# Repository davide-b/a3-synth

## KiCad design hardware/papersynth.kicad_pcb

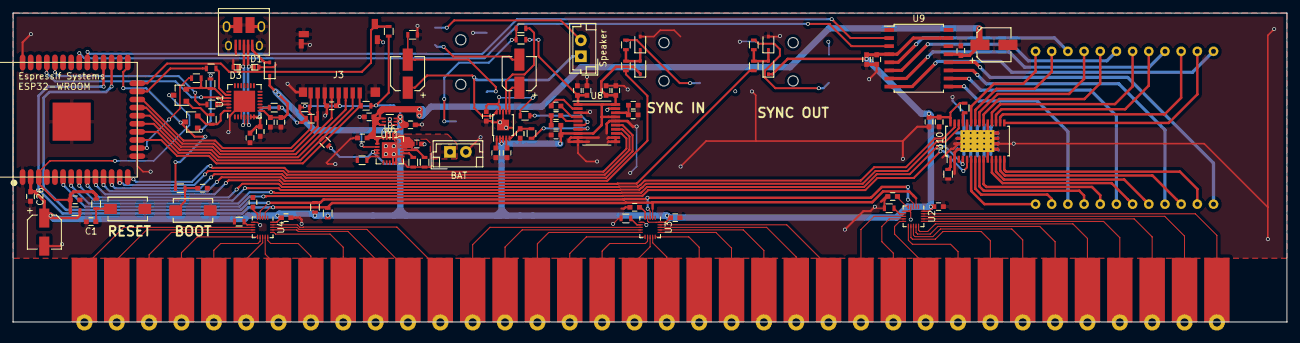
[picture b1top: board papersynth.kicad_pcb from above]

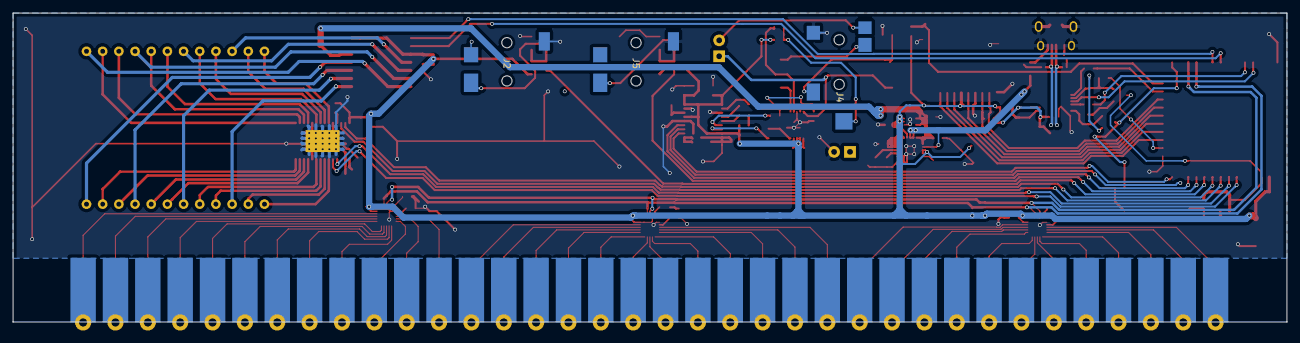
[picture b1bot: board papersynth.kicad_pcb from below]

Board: 2 copper layers, 200.0 x 48.5 mm, 106 parts (3 on the bottom side), 135 nets.

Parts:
BT1: BAT; JST_EH_B02B-EH-A_02x2.50mm_Straight
C1, C2, C24: 1nF; C_0603
C3, C5, C20, C27, C28, C30, C37, C40, C42: 10uF; C_0603
C4, C6, C7, C8, C9, C10, C11, C12, C19, C21, C22, C23, C29, C38, C39: 0.1uF; C_0603
C13, C14: 4.7uF; C_0603
C15, C16, C26, C33, C34: 1uF; C_0603
C17, C18: 2.2uF; C_0603
C25, C41: 100uF; CP_Elec_5x5.3
C31, C32: 2.2nF; C_0603
C35, C36: 100uF; CP_Elec_5x5.3_0603-capable
D1, D3: ESD05V88D-LC; D_SOD-882
D2, D4, D5, D6, D7: D_Schottky; D_SOD-323
J1: USB_OTG; USB_Micro-B_10103594-0001LF
J2, J5: JACK_2P; JACK3.5mm_MJ1-3510-SMT
J3: Micro_SD_Card_Det; MicroSD_PushIn-PullOut_card-detect
J4: JACK_TRS_5PINS; 35RASMT4BHNTRX
LS1: Speaker; JST_EH_B02B-EH-A_02x2.50mm_Straight
Q1, Q2: Q_NPN_BEC; SOT-23
R1, R2, R17, R18, R19, R20: 5.1k; R_0603
R3, R4, R22: 12k; R_0603
R5, R6, R9, R28, R29: 470; R_0603
R7, R8: 0R; R_0603
R10, R11, R12: 75k; R_0603
R13, R21, R27, R33: 10k; R_0603
R14: 6.8k; R_0603
R15: 2.8k; R_0603
R16: 2k; R_0603
R23, R25: 10R; R_0603
R24, R26: 300; R_0603
R30, R31: 100k; R_0603
R32: 1k; R_0603
SW1, SW2: SW_Push; SW_SPST_EVQPE1
U1: CP2102; QFN-28-1EP_5x5mm_Pitch0.5mm_cornerPad
U2, U3, U4: MPR121; UQFN-20-1EP_3x3mm_Pitch0.4mm_nopad
U5: FINGER_CONN_36; 36pin_IO_finger_interface
U6: MCP73871; QFN-20-1EP_4x4mm_Pitch0.5mm
U7: 8x8_LED_MATRIX_RG; 8x8_RG_LED_MATRIX
U8: PCM5102A; TSSOP-20_4.4x6.5mm_Pitch0.65mm
U9: MIC5891; SOIC-16W_7.5x10.3mm_Pitch1.27mm
U10: PCA9745B; HTSSOP-28_4.4x9.7mm_Pitch0.65mm_SmallThermalPad
U11: LDL212PU33R; DFN-6-1EP_2x2mm_Pitch0.5mm
U12: ESP-WROOM-32; ESP32-WROOM
U13: TPA0253; MSOP-10-1EP_3x3mm_Pitch0.5mm

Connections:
+3V3: C3.1, C4.1, C7.1, C8.1, C9.1, C16.1, C19.1, C20.1, C21.1, C23.1, C25.1, C26.1, C27.1, C29.1, C30.1, C38.1, C39.1, C40.1, C42.1, D4.1, D6.1, J3.4, R1.1, R2.1, R17.1, R18.1, R19.1, R20.1, R21.1, R22.1, R27.2, R31.2, R33.2, U1.6, U1.7, U2.20, U3.4, U3.20, U4.20, U6.3, U6.4, U6.17, U8.1, U8.8, U8.17, U8.20, U9.4, U9.15, U10.28, U11.2, U11.3, U12.2, U13.2, U13.3
+5V: C5.1, C6.1, D2.1, U1.8, U6.2, U6.18, U6.19
+BATT: BT1.1, C14.1, U6.14, U6.15, U6.16
/AUDIO_INTERFACE/BCLK: U8.13, U12.14
/AUDIO_INTERFACE/DACDAT: U8.14, U12.13
/AUDIO_INTERFACE/LRCLK: U8.15, U12.12
/ESP32_MODULE/COL_C: U10.26, U12.8
/ESP32_MODULE/COL_D: U10.27, U12.9
/ESP32_MODULE/COL_LAT: U10.4, U12.7
/ESP32_MODULE/COL_OE: U10.5, U12.6
/ESP32_MODULE/EN: C24.1, Q1.3, R5.1, R22.2, U12.3
/ESP32_MODULE/GPIO0: Q2.3, R6.1, U12.25
/ESP32_MODULE/GPIO13: R8.2, U12.16
/ESP32_MODULE/GPIO15: R7.2, U12.23
/ESP32_MODULE/ROW_C: U9.2, U12.30
/ESP32_MODULE/ROW_D: U9.3, U12.31
/ESP32_MODULE/SCL: R1.2, U2.2, U3.2, U4.2, U12.28
/ESP32_MODULE/SDA: R2.2, U2.3, U3.3, U4.3, U4.4, U12.27
/ESP32_MODULE/SYNC_IN: R26.2, U12.11
/ESP32_MODULE/SYNC_OUT: R24.2, U12.10
/ESP32_MODULE/U0RXD: R9.2, U12.34
/ESP32_MODULE/U0TXD: U1.25, U12.35
/LED_DISPLAY/K1G: U7.24, U10.23
/LED_DISPLAY/K1R: U7.23, U10.22
/LED_DISPLAY/K2G: U7.21, U10.21
/LED_DISPLAY/K2R: U7.20, U10.20
/LED_DISPLAY/K3G: U7.18, U10.18
/LED_DISPLAY/K3R: U7.17, U10.17
/LED_DISPLAY/K4G: U7.15, U10.16
/LED_DISPLAY/K4R: U7.14, U10.15
/LED_DISPLAY/K5G: U7.1, U10.6
/LED_DISPLAY/K5R: U7.2, U10.7
/LED_DISPLAY/K6G: U7.4, U10.8
/LED_DISPLAY/K6R: U7.5, U10.9
/LED_DISPLAY/K7G: U7.7, U10.11
/LED_DISPLAY/K7R: U7.8, U10.12
/LED_DISPLAY/K8G: U7.10, U10.13
/LED_DISPLAY/K8R: U7.11, U10.14
CARDET: J3.9, R21.2, U12.24
CMD: J3.3, U12.19
CTS: R7.1, U1.23
DAT0: J3.7, R17.2, U12.21
DAT1: J3.8, R18.2, U12.22
DAT2: J3.1, R19.2, U12.17
DAT3: J3.2, R20.2, U12.18
DTR: Q2.2, R3.2, U1.28
GND: BT1.2, C1.2, C2.2, C3.2, C4.2, C5.2, C6.2, C7.2, C8.2, C9.2, C10.2, C11.2, C12.2, C13.2, C14.2, C15.2, C16.2, C18.1, C19.2, C20.2, C21.2, C22.2, C23.2, C24.2, C25.2, C26.2, C27.2, C28.2, C29.2, C30.2, C31.1, C32.2, C33.2, C34.2, C37.2, C38.2, C39.2, C40.2, C41.2, C42.2, D1.2, D3.2, D5.2, D7.2, J1.5, J1.6, J2.1, J3.6, J3.10, J3.11, J4.1, J5.1, R10.2, R11.1, R12.2, R13.1, R14.1, R15.1, R16.2, R32.1, SW1.1, SW2.1, U1.3, U1.29, U1.30, U2.4, U2.6, U3.6, U4.6, U6.9, U6.10, U6.11, U6.21, U8.3, U8.9, U8.10, U8.11, U8.12, U8.16, U8.19, U9.1, U9.14, U10.2, U10.10, U10.19, U10.24, U10.29, U11.1, U11.7, U12.1, U12.15, U12.38, U12.39, U13.8, U13.11
unnamed: C1.1, R5.2, SW1.2
unnamed: C2.1, R6.2, SW2.2
unnamed: C10.1, U2.5
unnamed: C11.1, U3.5
unnamed: C12.1, U4.5
unnamed: C17.1, U8.4
unnamed: C17.2, U8.2
unnamed: C18.2, U8.5
unnamed: C22.1, C28.1, U8.18
unnamed: C31.2, R28.1, U13.5
unnamed: C32.1, R29.1, U13.9
unnamed: C33.1, U13.4
unnamed: C34.1, U13.1
unnamed: C35.1, U13.6
unnamed: C35.2, J4.3
unnamed: C36.1, LS1.1, U13.10
unnamed: C36.2, J4.2, R32.2
unnamed: D2.2, J1.1
unnamed: D4.2, D5.1, R23.2, R24.1
unnamed: D6.2, D7.1, R25.2, R26.1
unnamed: J2.2, R23.1
unnamed: J4.4, R30.1, R31.1
unnamed: J4.5, LS1.2
unnamed: J5.2, R25.1
unnamed: Q1.1, R3.1
unnamed: Q2.1, R4.1
unnamed: R9.1, U1.26
unnamed: R10.1, U4.7
unnamed: R11.2, U2.7
unnamed: R12.1, U3.7
unnamed: R13.2, U6.5
unnamed: R14.2, U6.12
unnamed: R15.2, U6.13
unnamed: R16.1, U10.1
unnamed: R27.1, U1.9
unnamed: R28.2, U8.7
unnamed: R29.2, U8.6
unnamed: R30.2, U13.7
unnamed: R33.1, U10.25
unnamed: U2.8, U5.12
unnamed: U2.9, U5.11
unnamed: U2.10, U5.10
unnamed: U2.11, U5.9
unnamed: U2.12, U5.8
unnamed: U2.13, U5.7
unnamed: U2.14, U5.6
unnamed: U2.15, U5.5
unnamed: U2.16, U5.4
unnamed: U2.17, U5.3
unnamed: U2.18, U5.2
unnamed: U2.19, U5.1
unnamed: U3.8, U5.24
unnamed: U3.9, U5.23
unnamed: U3.10, U5.22
unnamed: U3.11, U5.21
unnamed: U3.12, U5.20
unnamed: U3.13, U5.19
unnamed: U3.14, U5.18
unnamed: U3.15, U5.17
unnamed: U3.16, U5.16
unnamed: U3.17, U5.15
unnamed: U3.18, U5.14
unnamed: U3.19, U5.13
unnamed: U4.8, U5.36
unnamed: U4.9, U5.35
unnamed: U4.10, U5.34
unnamed: U4.11, U5.33
unnamed: U4.12, U5.32
unnamed: U4.13, U5.31
unnamed: U4.14, U5.30
unnamed: U4.15, U5.29
unnamed: U4.16, U5.28
unnamed: U4.17, U5.27
unnamed: U4.18, U5.26
unnamed: U4.19, U5.25
unnamed: U7.3, U9.9
unnamed: U7.6, U9.10
unnamed: U7.9, U9.11
unnamed: U7.12, U9.12
unnamed: U7.13, U9.8
unnamed: U7.16, U9.7
unnamed: U7.19, U9.6
unnamed: U7.22, U9.5
RTS: Q1.2, R4.2, R8.1, U1.24
SDCLK: J3.5, U12.20
USB_DM: D1.1, J1.2, U1.5
USB_DP: D3.1, J1.3, U1.4
VUNREG: C13.1, C15.1, C37.1, C41.1, U6.1, U6.20, U9.13, U11.4, U11.6

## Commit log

2017-08-29 Substituted RGB matrix with RG matrix
2017-08-30 Added PCA9745B part
2017-08-30 Substituted LED PWM driver
2017-08-30 Re-generated netlist
2017-08-30 Routed LED drivers
2017-08-30 Routed audio out
2017-08-30 Routed USB adapter
2017-08-31 Routed power management
2017-09-01 Fixed library problems and re-generated netlist
2017-09-10 Finished routing
2017-09-10 Added solder mask keep out
2017-09-23 Swapped side of jacks
2017-09-23 Stitched some planes
2017-10-06 Swapped connector side
2017-12-21 Version sent out for manufacturing on 2017-12-20
2017-12-21 ingored gerbers
